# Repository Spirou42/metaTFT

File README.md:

#  metaTFT
A litte UI package (hardware / software) for building simple list like UIs for µcontroller projects. 

## Hardware
The hardware is split up into 3 main parts.

1. small 2.2" [TFT Display](http://ledsee.com/index.php/en/lcd-display/2-2-inch-tft-spi-serial-240-x-320-detail) with SPI interface and SD card reader.
2. [5 keys](http://www.mec.dk/12-26847-Series-details.php?id=289) arranged as a [cursor cross with unmarked caps](http://www.mec.dk/files/MEC/brochures/MEC_ProductCatalogueno7_navimec.pdf) and a legacy [hollow shaft encoder](http://www.mouser.de/Search/ProductDetail.aspx?R=EC60A1520404virtualkey68800000virtualkey688-EC60A1520404)
3. Interface split & Signal conditioning 

The three components / boards are interconnected by standard ribbon cable with [microMaTch](http://www.te.com/deu-de/products/connectors/pcb-connectors/wire-to-board-connectors/ffc-fpc-ribbon-connectors/intersection/micro-match.html?n=125835&type=products&tab=pgp-product) connectors 

### Boards
#### 1. TFT board
The TFT board is a small connector board only holding the ribbon cable connector and the transistor for the backlight control.
![dispb]

#### 2. Key board
![encb]

#### 3. Debouncer
![debb]

## Software

[olduif]: Assets/oldUIfront.jpg "Old UI"
[olduib]: Assets/oldUIback.jpg "Old UI backside"
[encb]: Assets/EncoderBaseSmall.jpg "Encoder Board"
[dispb]: Assets/DisplayBoardSmall.jpg "Display Board"
[debb]: Assets/DebouncerSmall.jpg "Debouncer"
[tftani]: Assets/TFTBoard.mp4 "TFTBoard"

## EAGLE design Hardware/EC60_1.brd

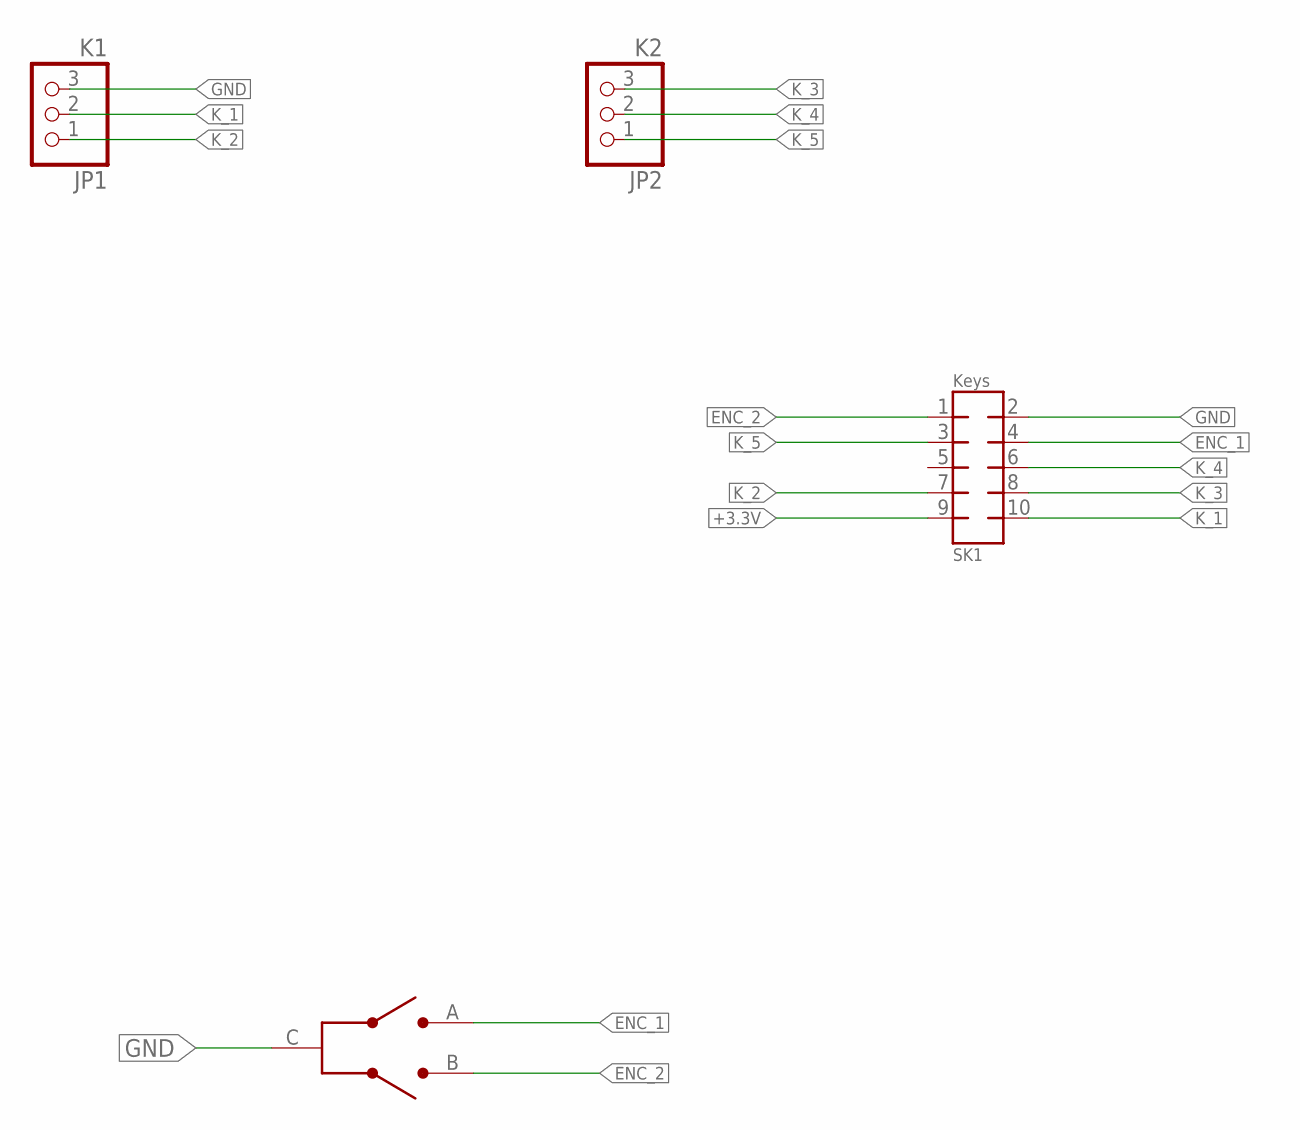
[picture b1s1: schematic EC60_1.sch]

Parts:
JP1: K1; 1X03
JP2: K2; 1X03
SK1: Keys; AMP-215079-10
U$1: EC60A

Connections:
+3.3V: SK1.9
ENC_1: SK1.4, U$1.A
ENC_2: SK1.1, U$1.B
GND: JP1.3, SK1.2, U$1.C
K_1: JP1.2, SK1.10
K_2: JP1.1, SK1.7
K_3: JP2.3, SK1.8
K_4: JP2.2, SK1.6
K_5: JP2.1, SK1.3

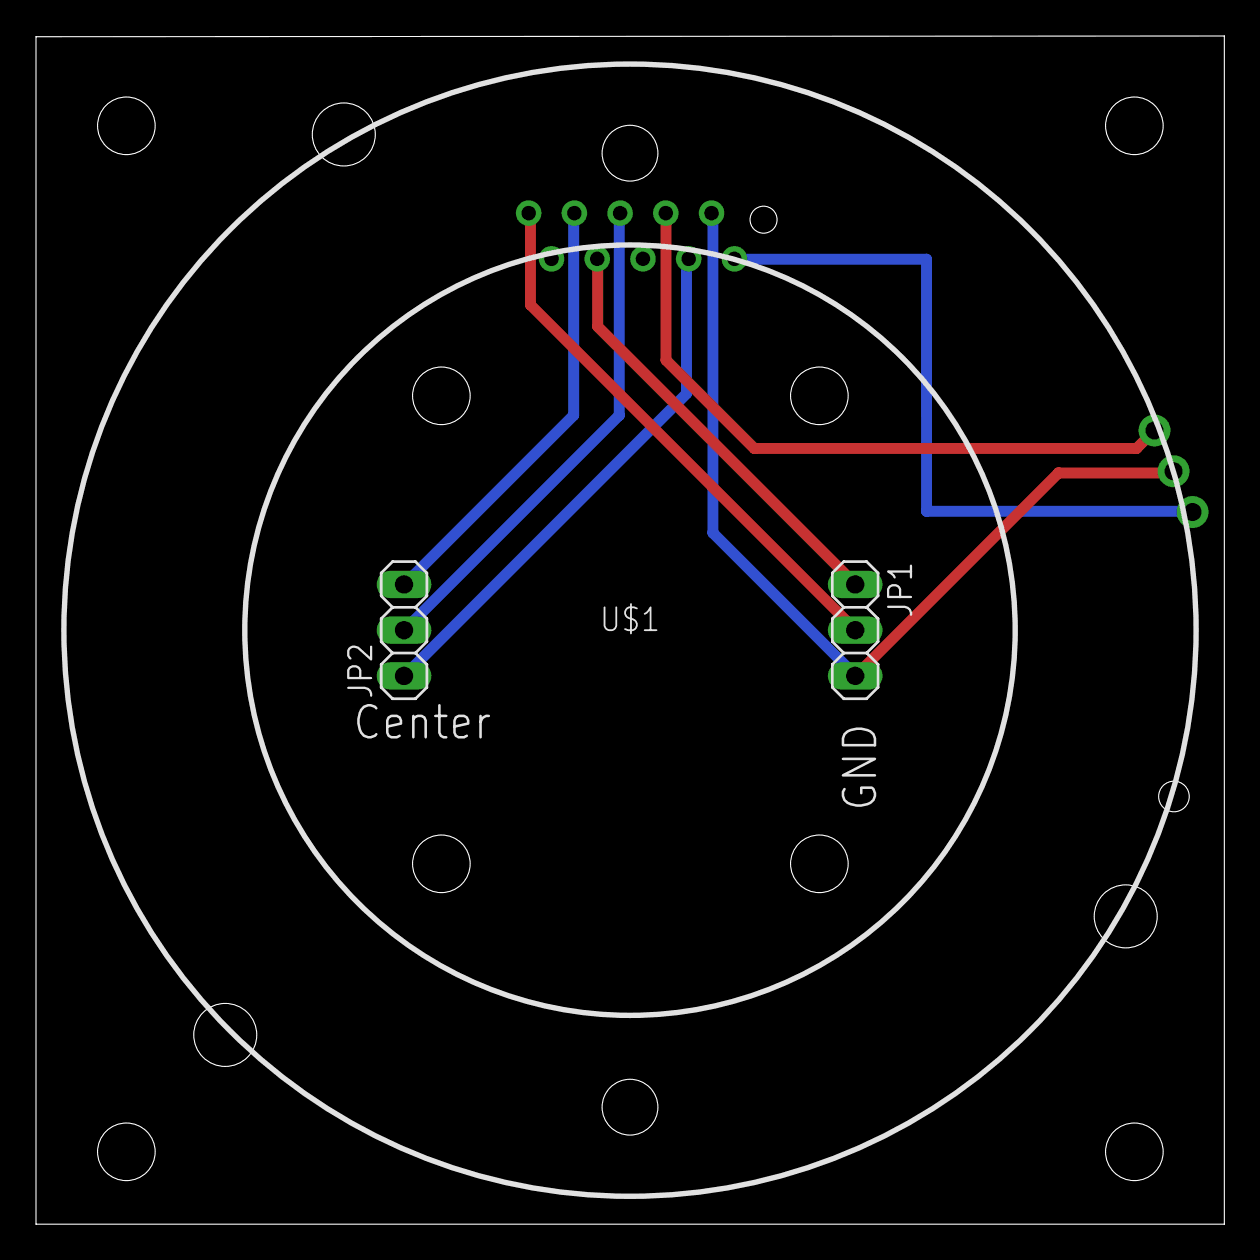
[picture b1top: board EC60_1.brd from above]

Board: 2 copper layers, 66.0 x 66.0 mm, 4 parts (1 on the bottom side), 8 nets.

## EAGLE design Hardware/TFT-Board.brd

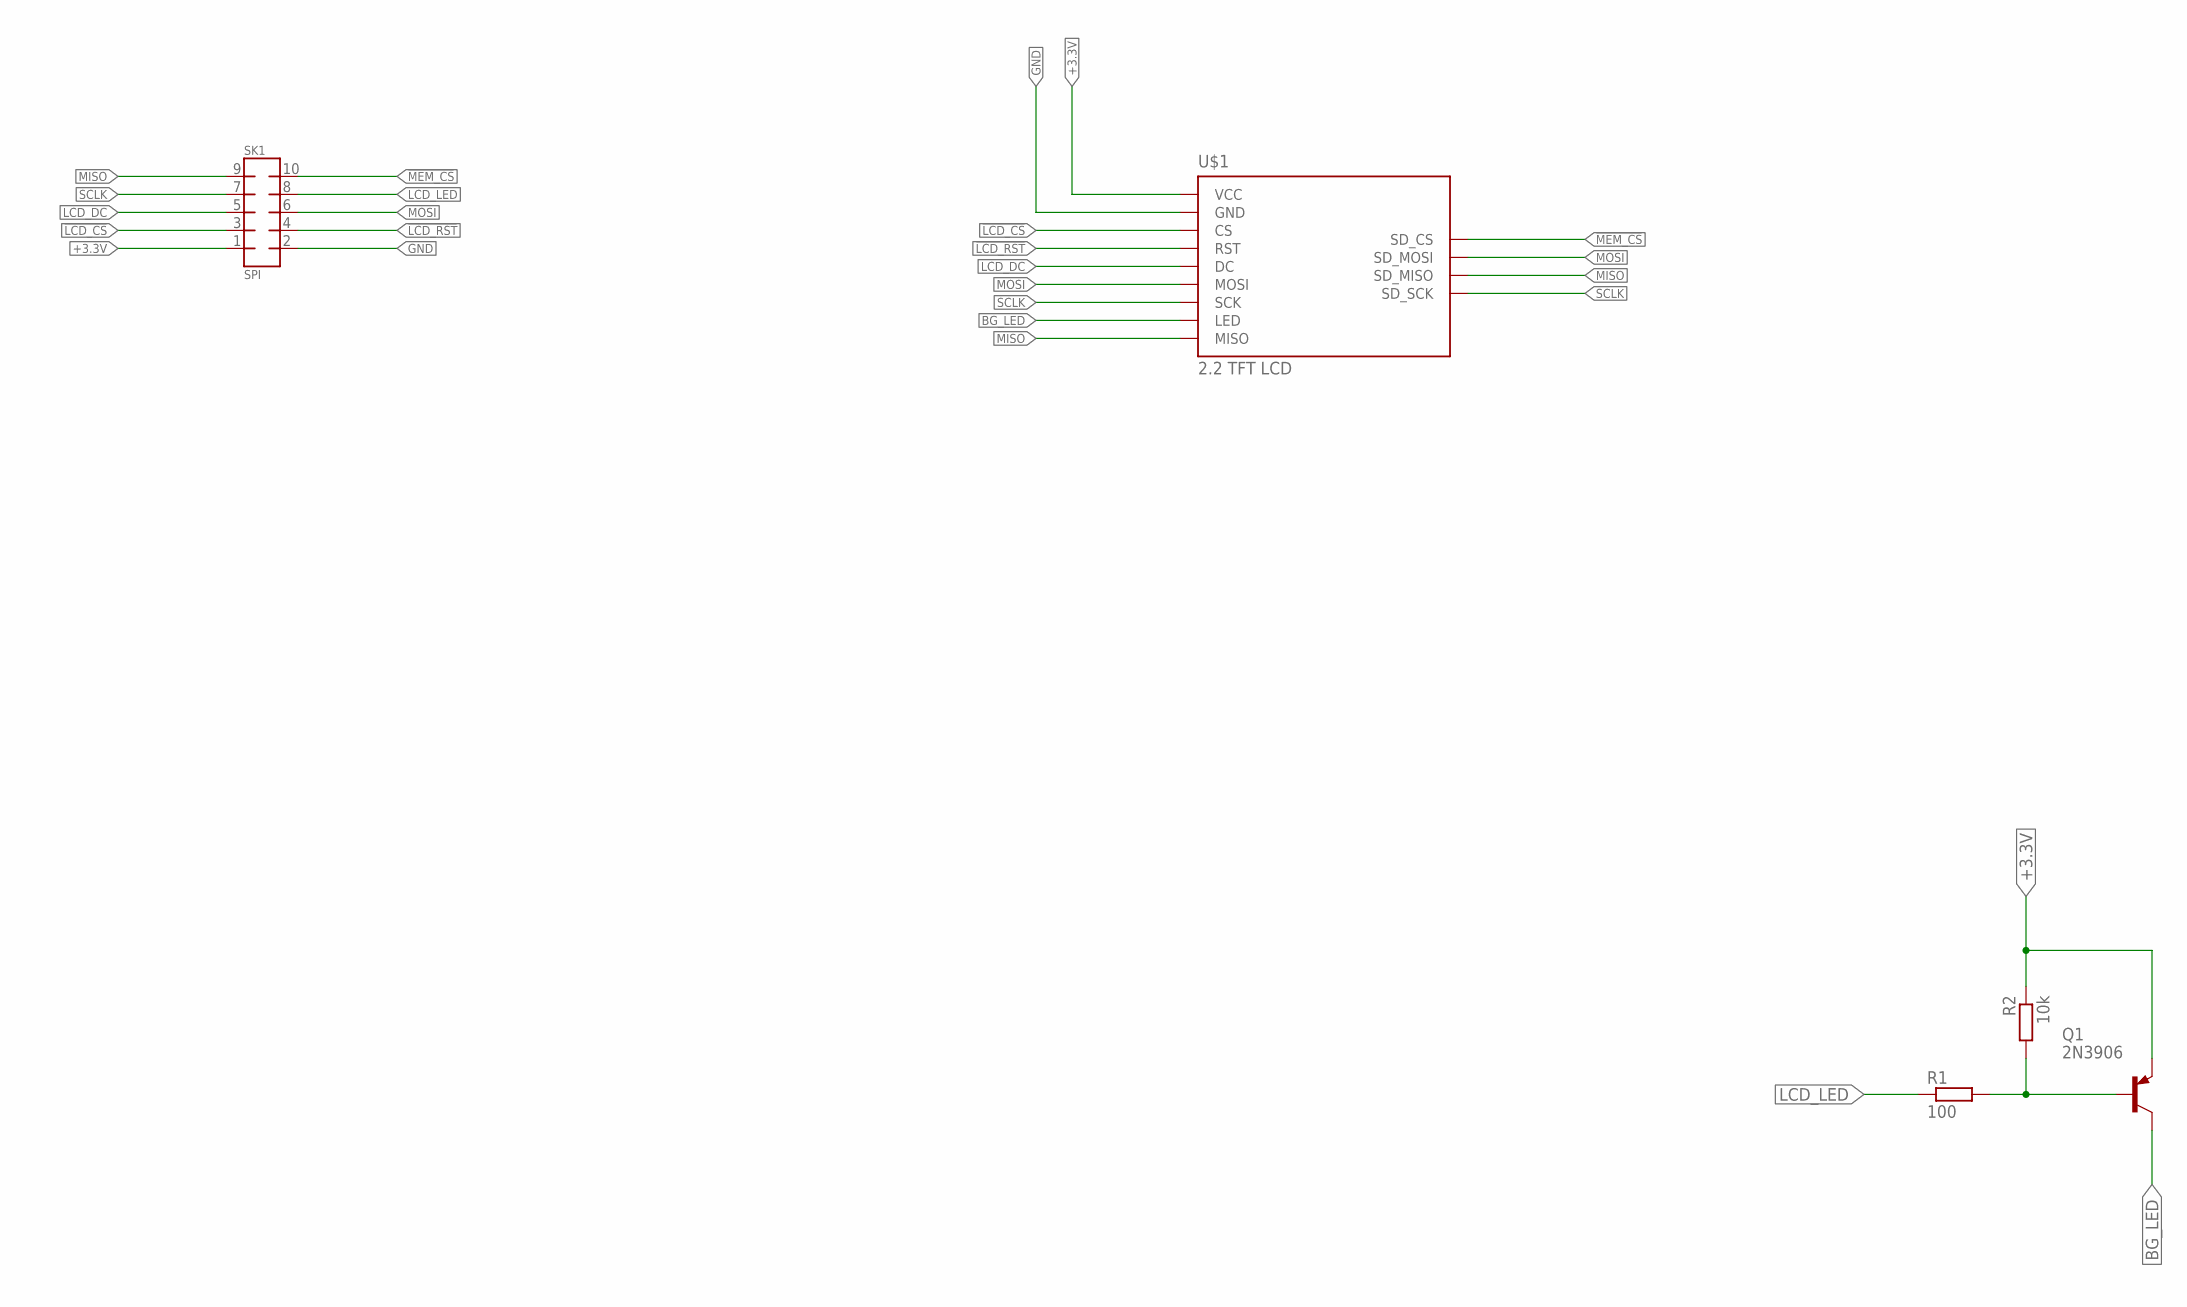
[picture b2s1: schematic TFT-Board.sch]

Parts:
Q1: 2N3906; TO92
R1: 100; 0204/7
R2: 10k; 0204/7
SK1: SPI; AMP-215079-10
U$1: 2.2_TFT_LCDNEW; 2.2_TFT_LCD_LEDSEE

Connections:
!LCD_CS: SK1.3, U$1.P$3_CS (CS)
!LCD_RST: SK1.4, U$1.P$2_RESET (RST)
!MEM_CS: SK1.10, U$1.P$2_SD_CS (SD_CS)
+3.3V: Q1.3 (E), R2.1, SK1.1, U$1.P$5_VCC (VCC)
BG_LED: Q1.1 (C), U$1.P$8_LED (LED)
GND: SK1.2, U$1.P$4_GND (GND)
LCD_DC: SK1.5, U$1.P$1_DC (DC)
LCD_LED: R1.1, SK1.8
MISO: SK1.9, U$1.P$3_SD_MISO (SD_MISO), U$1.P$9_MISO (MISO)
MOSI: SK1.6, U$1.P$1_SD_MOSI (SD_MOSI), U$1.P$6_MOSI (MOSI)
unnamed: Q1.2 (B), R1.2, R2.2
SCLK: SK1.7, U$1.P$4_SD_SCK (SD_SCK), U$1.P$7_SCK (SCK)

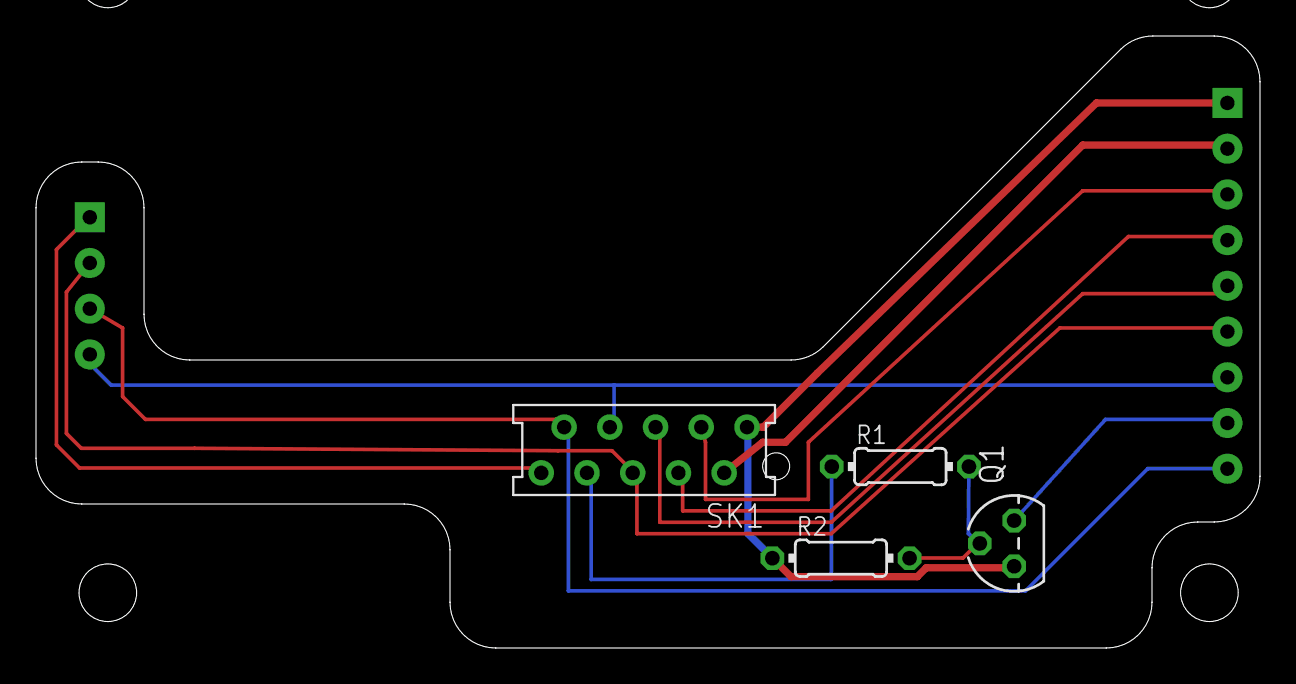
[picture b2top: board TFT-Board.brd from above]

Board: 2 copper layers, 68.0 x 34.0 mm, 5 parts (1 on the bottom side), 12 nets.

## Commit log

2016-09-04 No ds store
2016-09-04 Hardware Initial commit
2016-09-04 cleaning up
2016-09-05 added documentation stubs
2016-09-06 Renaming headers
2016-09-06 Renaming files
2016-09-06 Header renaming 2
2016-09-06 New parameters menu
2016-09-06 redraw parameter
2016-09-07 Anden preliminary doxyfile
2016-09-07 straighten files
2016-09-07 renaming metaAction
    Better name: ValueEditor
2016-09-07 Redrawing
2016-09-13 cleanup
2016-09-13 Added scroll indicator to metaList
2016-09-15 adding scrollIndicator sup
2016-09-15 better redraw
2016-09-19 prepare for custom list outlines
2016-09-20 custom outline drawing for Scrollable lists
2016-09-20 Nicer ScrollIndicator
2016-09-20 updated doc
2016-09-21 updating documentation
2017-12-05 adding some minor tweaks
2017-12-08 Rework for new project
2017-12-08 Preparing Arduino Library move
2017-12-08 switching to Arduino Library
2017-12-08 Removing obsolete files and getting the example to compile
2017-12-08 Adding some Readmes
2017-12-09 Arduino Library up and running
2017-12-10 spelling and some cleanUp
2017-12-10 cleanup Effects
2017-12-10 adding second example
2017-12-11 Effects bla
2017-12-14 Adding IR support
2017-12-15 Cleanup again
2017-12-15 addapt to changes in the Addons
2017-12-15 Moving EffectList to FastLEDAddOns
2017-12-16 prepare for IR Input
2017-12-16 Switching to namespaces for globals
2017-12-17 Added a bit fire
2017-12-17 More beautiful
2017-12-18 Adjustable Framerate for effects, Noise Effect - preparing for user adjustable parameters.
2017-12-18 running effects
2017-12-18 minor effect changes
2017-12-21 Renaming stuff
2017-12-21 prepare for IR control
2017-12-21 Oops
2017-12-22 spacing
2017-12-22 Adding first IRCodes
2017-12-28 Adding themes to Torch
2017-12-28 remove the bloddy flipping
2018-01-01 Doing the twist, adding new test feature
2018-01-02 Doing the twist - added a new effect
2018-01-03 adding setters for parameter names and min/max values
2018-01-03 Tweaking Lava - not good
2018-01-03 Disable Lava temporarely
2018-01-03 Adding ValueStore setter
2018-01-03 adding parameter for Rain Effect
2018-01-03 playing around
2018-01-11 Tweaking stuff
2018-01-24 Starting a Lava Effect
2018-03-05 Some Changes
